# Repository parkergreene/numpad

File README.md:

# numpad
Numpad built with rpi pico and circuit python

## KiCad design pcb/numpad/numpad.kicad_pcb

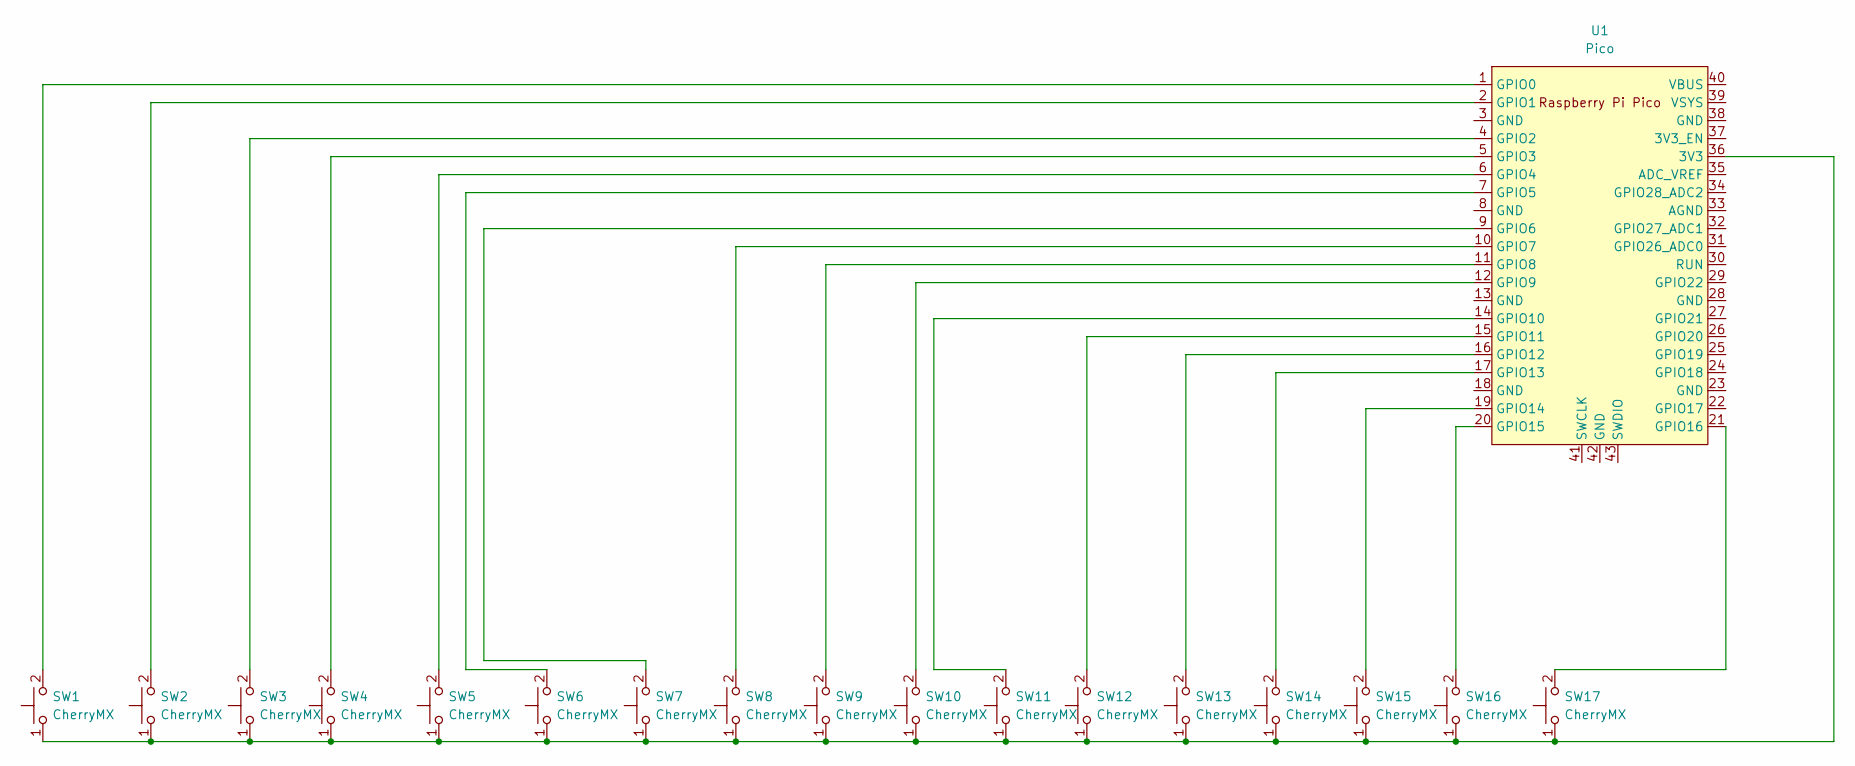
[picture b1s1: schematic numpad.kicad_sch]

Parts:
SW1, SW2, SW3, SW4, SW5, SW6, SW7, SW8, SW9, SW10, SW11, SW12, SW13, SW14: CherryMX; CherryMX_1.00u
SW15, SW16, SW17: CherryMX; CherryMX_2.00u
U1: Pico; RPi_Pico_SMD_TH

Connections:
unnamed: SW1.1, SW2.1, SW3.1, SW4.1, SW5.1, SW6.1, SW7.1, SW8.1, SW9.1, SW10.1, SW11.1, SW12.1, SW13.1, SW14.1, SW15.1, SW16.1, SW17.1, U1.36 (3V3)
unnamed: SW1.2, U1.1 (GPIO0)
unnamed: SW2.2, U1.2 (GPIO1)
unnamed: SW3.2, U1.4 (GPIO2)
unnamed: SW4.2, U1.5 (GPIO3)
unnamed: SW5.2, U1.6 (GPIO4)
unnamed: SW6.2, U1.7 (GPIO5)
unnamed: SW7.2, U1.9 (GPIO6)
unnamed: SW8.2, U1.10 (GPIO7)
unnamed: SW9.2, U1.11 (GPIO8)
unnamed: SW10.2, U1.12 (GPIO9)
unnamed: SW11.2, U1.14 (GPIO10)
unnamed: SW12.2, U1.15 (GPIO11)
unnamed: SW13.2, U1.16 (GPIO12)
unnamed: SW14.2, U1.17 (GPIO13)
unnamed: SW15.2, U1.19 (GPIO14)
unnamed: SW16.2, U1.20 (GPIO15)
unnamed: SW17.2, U1.21 (GPIO16)

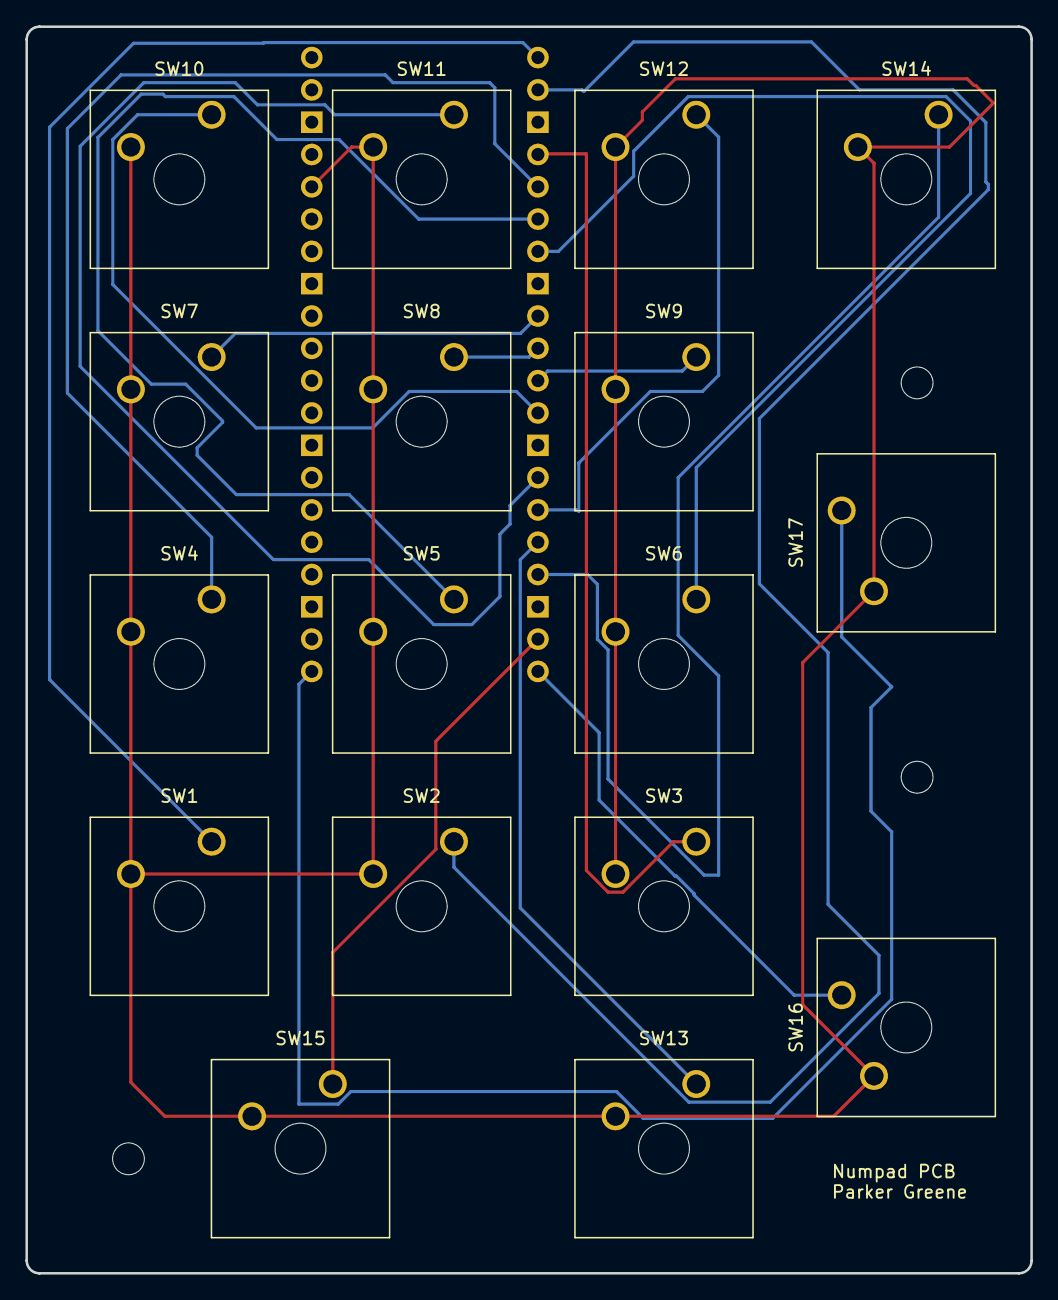
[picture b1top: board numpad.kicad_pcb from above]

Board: 2 copper layers, 79.0 x 98.0 mm, 18 parts (1 on the bottom side), 18 nets.

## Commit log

2023-12-31 init commit
2023-12-31 added kicad files
2024-01-01 added case stl file
